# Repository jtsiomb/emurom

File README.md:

emurom - ROM emulator board
===========================

The purpose of emurom is to make it fast and convenient to hack code in ROMs
without having to repeatedly remove and reprogram an actual ROM chip.

Emurom is a board which connects through USB to a host computer, and
can be connected in place of a parallel ROM chip on a target device. It acts as
a ROM chip, but holds its data in a static RAM, which can be updated at any time
through the USB connection. Optionally it can provide power (5v) to the device
by shorting a jumper, and it also has a lead to clip to the reset signal of the
target device, to automatically reboot it when a new ROM image is uploaded.

Hardware design (kicad project) is in the root directory. The firmware for the
microcontroller is located under `fw`, while in the `emurom` subdirectory, there
is a UNIX program which can be used to upload a ROM image to the device, simply
by running it with the name of the ROM image as a command line argument.

 - Project website: http://nuclear.mutantstargoat.com/hw/emurom
 - Git repository: https://github.com/jtsiomb/emurom
 - Schematic (PDF): http://nuclear.mutantstargoat.com/hw/emurom/emurom-schematic.pdf

License
-------
Copyright (C) 2020 John Tsiombikas <nuclear@member.fsf.org>

All hardware designs in this project are free/open hardware. Feel free to
manufacture, sell, use, modify and/or redistribute, under the terms of the
Creative Commons Attribution Share-Alike license (CC BY-SA). See `LICENSE.hw`
for details.

All software in this project (firmware and host upload program) are free
software. Feel free to use, modify and/or redistribute under the terms of the
GNU General Public License version 3, or at your option any later version
published by the Free Software foundation. See `LICENSE.sw` for details.

Download
--------
This git repository contains the current project files and source code for
emurom, but it does not include any binaries or build products.

The release archive includes the schematic PDF, gerber files for PCB
manufacturing, datasheets, and pre-built binaries (firmware image and host
program).

Latest release (emurom rev2):
 - emurom website: http://nuclear.mutantstargoat.com/hw/emurom/release/emurom-rev2.tar.gz
 - github mirror: https://github.com/jtsiomb/emurom/releases/download/v2/emurom-rev2.tar.gz

Bill of materials
-----------------
Emurom rev2 BOM:

|#  | name    | description                                    | package       |
|---|---------|------------------------------------------------|---------------|
| 1 | U1      | ATmega328P AVR microcontroller                 | TQFP 32       |
| 1 | U2      | MCP2221 USB-serial converter                   | SOIC 14       |
| 1 | U3      | 74HCT157 quad 2-1 multiplexer                  | SOIC 16       |
| 2 | U4,U5   | 74HCT595 8-bit shift register w/3-state output | SOIC 16       |
| 1 | U6      | UM61512AK 64k static RAM (or similar 64k SRAMs)| PDIP 32       |
| 3 | U7-U9   | 74HCT244 octal 3-state buffer                  | SOIC 20       |
| 2 | C1,C2   | 22 pF ceramic capacitor                        | 0805          |
|11 | C3-C13  | 0.1 uF ceramic capacitor                       | 0805          |
| 2 | R1,R2   | 330 Ohm resistor                               | 0805          |
| 6 | R3-R8   | 4.7 kOhm resistor                              | 0805          |
| 2 | D1,D2   | LED                                            | 0805          |
| 2 | D3,D4   | 1N4148 signal diodes                           | 0805          |
| 1 | Y1      | 14.7456 quartz crystal                         | 7.6x4.1mm SMD |
| 3 | JP1-JP3 | 2-pin male header (jumper pins)                     |          |
| 1 | J1      | 6-pin (2x3) male header or IDC conn. 2.54mm pitch   |          |
| 1 | J2      | molex 105017-1001 micro-USB (type B) connector      |          |
| 1 | U10,J3  | 24-pin (2x12) male header or IDC conn. 2.54mm pitch |          |
| 1 | U11,J5  | 28-pin (2x14) male header or IDC conn. 2.54mm pitch |          |
| 1 | J7      | 1-pin male header                                   |          |

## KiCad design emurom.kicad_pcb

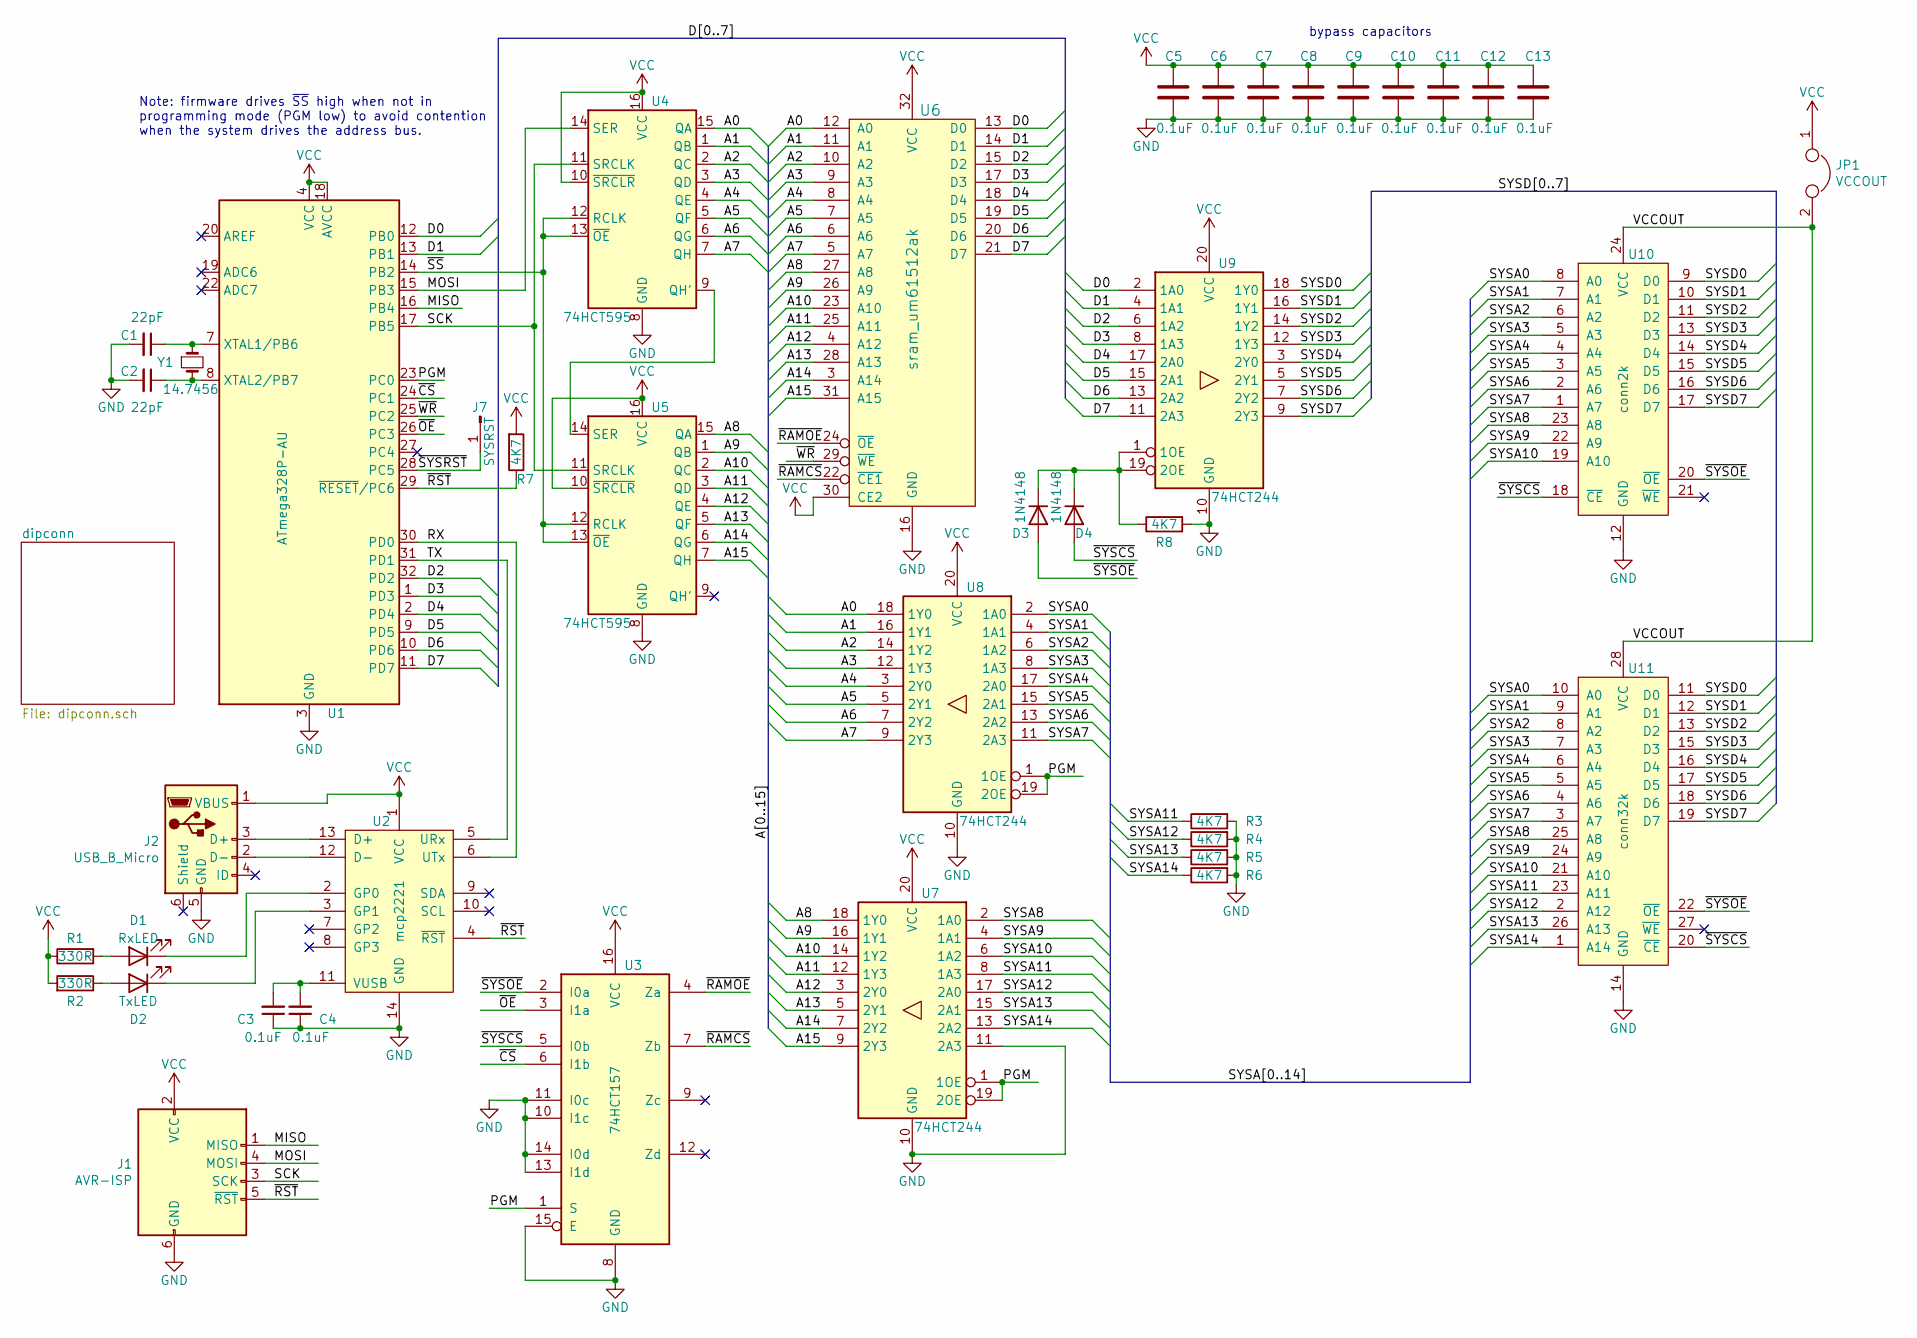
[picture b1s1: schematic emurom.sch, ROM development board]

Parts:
C1, C2: 22pF; C_0805_2012Metric_Pad1.15x1.40mm_HandSolder
C3, C4, C5, C6, C7, C8, C9, C10, C11, C12, C13: 0.1uF; C_0805_2012Metric_Pad1.15x1.40mm_HandSolder
D1: RxLED; LED_0805_2012Metric_Pad1.15x1.40mm_HandSolder
D2: TxLED; LED_0805_2012Metric_Pad1.15x1.40mm_HandSolder
D3, D4: 1N4148; D_0805_2012Metric_Pad1.15x1.40mm_HandSolder
J1: AVR-ISP; IDC-Header_2x03_P2.54mm_Vertical
J2: USB_B_Micro; USB_Micro-B_Molex-105017-0001
J7: SYSRST; PinSocket_1x01_P2.54mm_Vertical
JP1: VCCOUT; PinHeader_1x02_P2.54mm_Vertical
R1, R2: 330R; R_0805_2012Metric_Pad1.15x1.40mm_HandSolder
R3, R4, R5, R6, R7, R8: 4K7; R_0805_2012Metric_Pad1.15x1.40mm_HandSolder
U1: ATmega328P-AU; TQFP-32_7x7mm_P0.8mm
U2: mcp2221; SOIC-14_3.9x8.7mm_P1.27mm
U3: 74HCT157; SOIC-16_4.55x10.3mm_P1.27mm
U4, U5: 74HCT595; SOIC-16_3.9x9.9mm_P1.27mm
U6: sram_um61512ak; DIP-32_W7.62mm
U7, U8, U9: 74HCT244; SOIC-20W_7.5x12.8mm_P1.27mm
U10: conn2k
U11: conn32k
Y1: 14.7456; Crystal_SMD_ECS_CSM3X-2Pin_7.6x4.1mm

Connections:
/A0: U4.15 (QA), U6.12 (A0), U8.18 (1Y0)
/A1: U4.1 (QB), U6.11 (A1), U8.16 (1Y1)
/A2: U4.2 (QC), U6.10 (A2), U8.14 (1Y2)
/A3: U4.3 (QD), U6.9 (A3), U8.12 (1Y3)
/A4: U4.4 (QE), U6.8 (A4), U8.3 (2Y0)
/A5: U4.5 (QF), U6.7 (A5), U8.5 (2Y1)
/A6: U4.6 (QG), U6.6 (A6), U8.7 (2Y2)
/A7: U4.7 (QH), U6.5 (A7), U8.9 (2Y3)
/A8: U5.15 (QA), U6.27 (A8), U7.18 (1Y0)
/A9: U5.1 (QB), U6.26 (A9), U7.16 (1Y1)
/A10: U5.2 (QC), U6.23 (A10), U7.14 (1Y2)
/A11: U5.3 (QD), U6.25 (A11), U7.12 (1Y3)
/A12: U5.4 (QE), U6.4 (A12), U7.3 (2Y0)
/A13: U5.5 (QF), U6.28 (A13), U7.5 (2Y1)
/A14: U5.6 (QG), U6.3 (A14), U7.7 (2Y2)
/A15: U5.7 (QH), U6.31 (A15), U7.9 (2Y3)
/D0: U1.12 (PB0), U6.13 (D0), U9.2 (1A0)
/D1: U1.13 (PB1), U6.14 (D1), U9.4 (1A1)
/D2: U1.32 (PD2), U6.15 (D2), U9.6 (1A2)
/D3: U1.1 (PD3), U6.17 (D3), U9.8 (1A3)
/D4: U1.2 (PD4), U6.18 (D4), U9.17 (2A0)
/D5: U1.9 (PD5), U6.19 (D5), U9.15 (2A1)
/D6: U1.10 (PD6), U6.20 (D6), U9.13 (2A2)
/D7: U1.11 (PD7), U6.21 (D7), U9.11 (2A3)
/MISO: J1.1 (MISO), U1.16 (PB4)
/MOSI: J1.4 (MOSI), U1.15 (PB3), U4.14 (SER)
/PGM: U1.23 (PC0), U3.1 (S), U7.1 (1OE), U7.19 (2OE), U8.1 (1OE), U8.19 (2OE)
/RX: U1.30 (PD0), U2.6 (UTx)
/SCK: J1.3 (SCK), U1.17 (PB5), U4.11 (SRCLK), U5.11 (SRCLK)
/SYSA0: U8.2 (1A0), U10.8 (A0), U11.10 (A0)
/SYSA1: U8.4 (1A1), U10.7 (A1), U11.9 (A1)
/SYSA2: U8.6 (1A2), U10.6 (A2), U11.8 (A2)
/SYSA3: U8.8 (1A3), U10.5 (A3), U11.7 (A3)
/SYSA4: U8.17 (2A0), U10.4 (A4), U11.6 (A4)
/SYSA5: U8.15 (2A1), U10.3 (A5), U11.5 (A5)
/SYSA6: U8.13 (2A2), U10.2 (A6), U11.4 (A6)
/SYSA7: U8.11 (2A3), U10.1 (A7), U11.3 (A7)
/SYSA8: U7.2 (1A0), U10.23 (A8), U11.25 (A8)
/SYSA9: U7.4 (1A1), U10.22 (A9), U11.24 (A9)
/SYSA10: U7.6 (1A2), U10.19 (A10), U11.21 (A10)
/SYSA11: R3.1, U7.8 (1A3), U11.23 (A11)
/SYSA12: R4.1, U7.17 (2A0), U11.2 (A12)
/SYSA13: R5.1, U7.15 (2A1), U11.26 (A13)
/SYSA14: R6.1, U7.13 (2A2), U11.1 (A14)
/SYSD0: U9.18 (1Y0), U10.9 (D0), U11.11 (D0)
/SYSD1: U9.16 (1Y1), U10.10 (D1), U11.12 (D1)
/SYSD2: U9.14 (1Y2), U10.11 (D2), U11.13 (D2)
/SYSD3: U9.12 (1Y3), U10.13 (D3), U11.15 (D3)
/SYSD4: U9.3 (2Y0), U10.14 (D4), U11.16 (D4)
/SYSD5: U9.5 (2Y1), U10.15 (D5), U11.17 (D5)
/SYSD6: U9.7 (2Y2), U10.16 (D6), U11.18 (D6)
/SYSD7: U9.9 (2Y3), U10.17 (D7), U11.19 (D7)
/TX: U1.31 (PD1), U2.5 (URx)
/VCCOUT: JP1.2, U10.24 (VCC), U11.28 (VCC)
/~CS: U1.24 (PC1), U3.6 (I1b)
/~OE: U1.26 (PC3), U3.3 (I1a)
/~RAMCS: U3.7 (Zb), U6.22 (~CE1)
/~RAMOE: U3.4 (Za), U6.24 (~OE)
/~RST: J1.5 (~RST), R7.1, U1.29 (~RESET~/PC6), U2.4 (~RST)
/~SS: U1.14 (PB2), U4.12 (RCLK), U4.13 (~OE), U5.12 (RCLK), U5.13 (~OE)
/~SYSCS: D4.2 (A), U3.5 (I0b), U10.18 (~CE), U11.20 (~CE)
/~SYSOE: D3.2 (A), U3.2 (I0a), U10.20 (~OE), U11.22 (~OE)
/~SYSRST: J7.1, U1.28 (PC5)
/~WR: U1.25 (PC2), U6.29 (~WE)
GND: C1.2, C2.2, C3.1, C4.1, C5.2, C6.2, C7.2, C8.2, C9.2, C10.2, C11.2, C12.2, C13.2, J1.6 (GND), J2.5 (GND), R3.2, R4.2, R5.2, R6.2, R8.2, U1.3 (GND), U1.5 (GND), U1.21 (GND), U2.14 (GND), U3.8 (GND), U3.10 (I1c), U3.11 (I0c), U3.13 (I1d), U3.14 (I0d), U3.15 (E), U4.8 (GND), U5.8 (GND), U6.16 (GND), U7.10 (GND), U7.11 (2A3), U8.10 (GND), U9.10 (GND), U10.12 (GND), U11.14 (GND)
unnamed: C1.1, U1.7 (XTAL1/PB6), Y1.1
unnamed: C2.1, U1.8 (XTAL2/PB7), Y1.2
unnamed: C3.2, C4.2, U2.11 (VUSB)
unnamed: D1.1 (K), U2.2 (GP0)
unnamed: D1.2 (A), R1.2
unnamed: D2.1 (K), U2.3 (GP1)
unnamed: D2.2 (A), R2.1
unnamed: D3.1 (K), D4.1 (K), R8.1, U9.1 (1OE), U9.19 (2OE)
unnamed: J2.2 (D-), U2.12 (D-)
unnamed: J2.3 (D+), U2.13 (D+)
unnamed: U4.9 (QH'), U5.14 (SER)
VCC: C5.1, C6.1, C7.1, C8.1, C9.1, C10.1, C11.1, C12.1, C13.1, J1.2 (VCC), J2.1 (VBUS), JP1.1, R1.1, R2.2, R7.2, U1.4 (VCC), U1.6 (VCC), U1.18 (AVCC), U2.1 (VCC), U3.16 (VCC), U4.10 (~SRCLR), U4.16 (VCC), U5.10 (~SRCLR), U5.16 (VCC), U6.30 (CE2), U6.32 (VCC), U7.20 (VCC), U8.20 (VCC), U9.20 (VCC)

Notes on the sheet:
bypass capacitors
Note: firmware drives ~SS~ high when not in programming mode (PGM low) to avoid contention when the system drives the address bus.

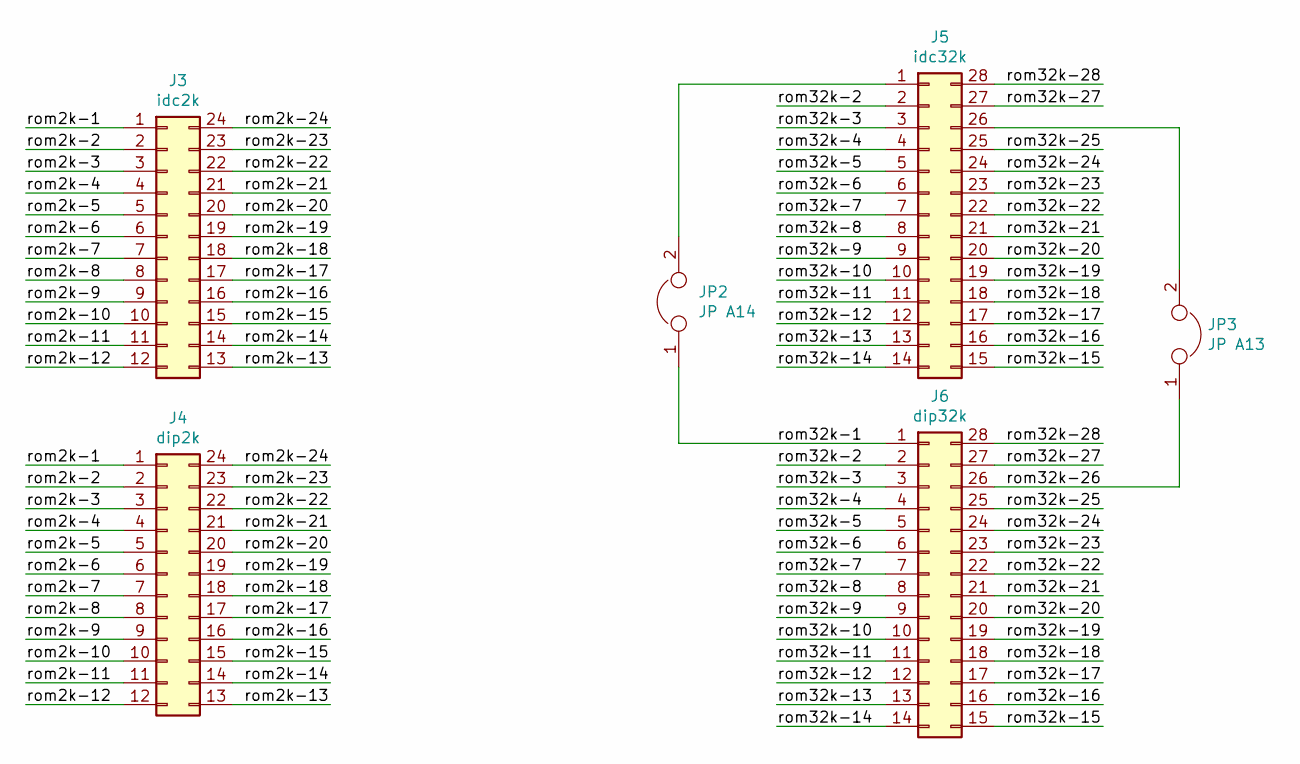
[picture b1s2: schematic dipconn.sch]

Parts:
J3: idc2k; conn2k
J4: dip2k; DIP-24_W15.24mm_Socket
J5: idc32k; conn32k
J6: dip32k; DIP-28_W15.24mm_Socket
JP2: JP A14; PinHeader_1x02_P2.54mm_Vertical
JP3: JP A13; PinHeader_1x02_P2.54mm_Vertical

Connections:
/dipconn/rom2k-1: J3.1, J4.1
/dipconn/rom2k-2: J3.2, J4.2
/dipconn/rom2k-3: J3.3, J4.3
/dipconn/rom2k-4: J3.4, J4.4
/dipconn/rom2k-5: J3.5, J4.5
/dipconn/rom2k-6: J3.6, J4.6
/dipconn/rom2k-7: J3.7, J4.7
/dipconn/rom2k-8: J3.8, J4.8
/dipconn/rom2k-9: J3.9, J4.9
/dipconn/rom2k-10: J3.10, J4.10
/dipconn/rom2k-11: J3.11, J4.11
/dipconn/rom2k-12: J3.12, J4.12
/dipconn/rom2k-13: J3.13, J4.13
/dipconn/rom2k-14: J3.14, J4.14
/dipconn/rom2k-15: J3.15, J4.15
/dipconn/rom2k-16: J3.16, J4.16
/dipconn/rom2k-17: J3.17, J4.17
/dipconn/rom2k-18: J3.18, J4.18
/dipconn/rom2k-19: J3.19, J4.19
/dipconn/rom2k-20: J3.20, J4.20
/dipconn/rom2k-21: J3.21, J4.21
/dipconn/rom2k-22: J3.22, J4.22
/dipconn/rom2k-23: J3.23, J4.23
/dipconn/rom2k-24: J3.24, J4.24
/dipconn/rom32k-1: J6.1, JP2.1
/dipconn/rom32k-2: J5.2, J6.2
/dipconn/rom32k-3: J5.3, J6.3
/dipconn/rom32k-4: J5.4, J6.4
/dipconn/rom32k-5: J5.5, J6.5
/dipconn/rom32k-6: J5.6, J6.6
/dipconn/rom32k-7: J5.7, J6.7
/dipconn/rom32k-8: J5.8, J6.8
/dipconn/rom32k-9: J5.9, J6.9
/dipconn/rom32k-10: J5.10, J6.10
/dipconn/rom32k-11: J5.11, J6.11
/dipconn/rom32k-12: J5.12, J6.12
/dipconn/rom32k-13: J5.13, J6.13
/dipconn/rom32k-14: J5.14, J6.14
/dipconn/rom32k-15: J5.15, J6.15
/dipconn/rom32k-16: J5.16, J6.16
/dipconn/rom32k-17: J5.17, J6.17
/dipconn/rom32k-18: J5.18, J6.18
/dipconn/rom32k-19: J5.19, J6.19
/dipconn/rom32k-20: J5.20, J6.20
/dipconn/rom32k-21: J5.21, J6.21
/dipconn/rom32k-22: J5.22, J6.22
/dipconn/rom32k-23: J5.23, J6.23
/dipconn/rom32k-24: J5.24, J6.24
/dipconn/rom32k-25: J5.25, J6.25
/dipconn/rom32k-26: J6.26, JP3.1
/dipconn/rom32k-27: J5.27, J6.27
/dipconn/rom32k-28: J5.28, J6.28
unnamed: J5.1, JP2.2
unnamed: J5.26, JP3.2

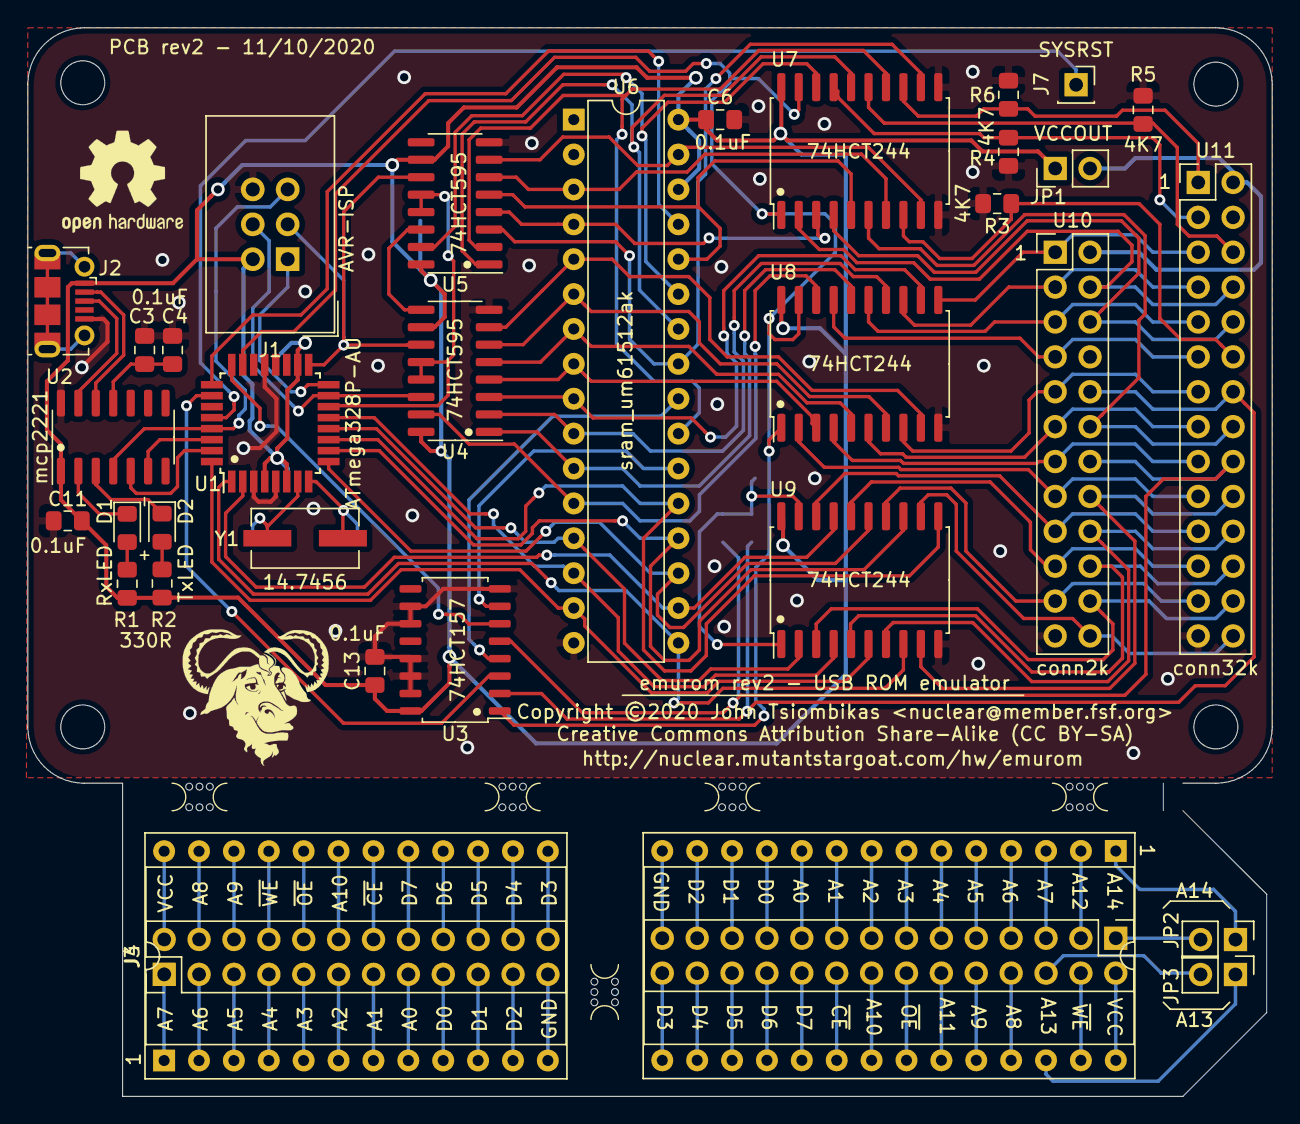
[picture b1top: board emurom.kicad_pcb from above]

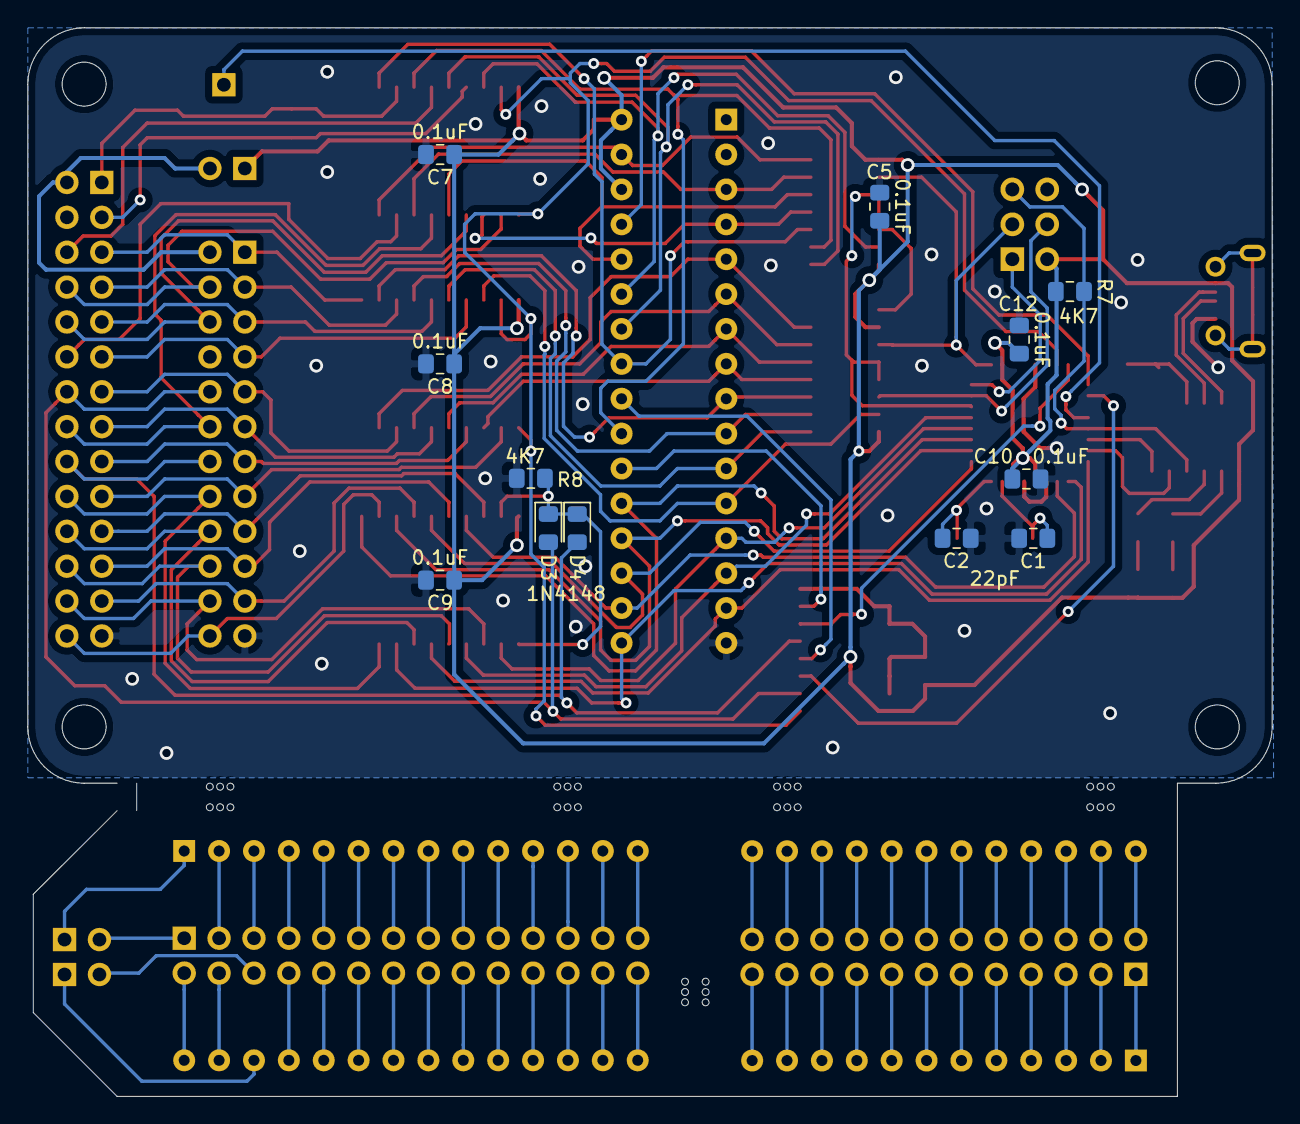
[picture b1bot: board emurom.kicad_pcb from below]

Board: 2 copper layers, 90.6 x 77.8 mm, 52 parts (12 on the bottom side), 131 nets.

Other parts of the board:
mouse-bite-2mm-slot, mouse-bite-2mm-slot#2, mouse-bite-2mm-slot#3, mouse-bite-2mm-slot#4, mouse-bite-2mm-slot#5: VAL**; mouse-bite-2mm-slot

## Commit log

2020-10-10 fixed swapped RX/TX lines
2020-10-10 - fixed mistake tying half the tri-state buffer bits to always on - fixed firmware bugs, now it can program and readback memory correctly
2020-10-13 fixed data bus output buffer enable
2020-10-13 emurom client program
2020-10-18 It works ... jesus FUCKING christ, I just had been feeding the address bus shift register backwards...
2020-10-18 renamed to emurom
2020-10-18 added README and LICENSE files
2020-10-18 updated readme and schematic info
2020-10-18 - attempt to fix issue #1 about the address jumpers being too close to the IDC connector. - added BOM and release links to the README
2020-10-18 minor README formatting fix
2023-12-27 version update

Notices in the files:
emurom.kicad_pcb:
Copyright ©2020 John Tsiombikas
Creative Commons Attribution Share-Alike (CC BY-SA)
emurom.sch:
License: Creative Commons Attribution Share-Alike (CC BY-SA)
